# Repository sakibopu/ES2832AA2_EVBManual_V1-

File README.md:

# ES2832AA2_EVBManual_V1 
 ES2832AA2_EVBManual_V1

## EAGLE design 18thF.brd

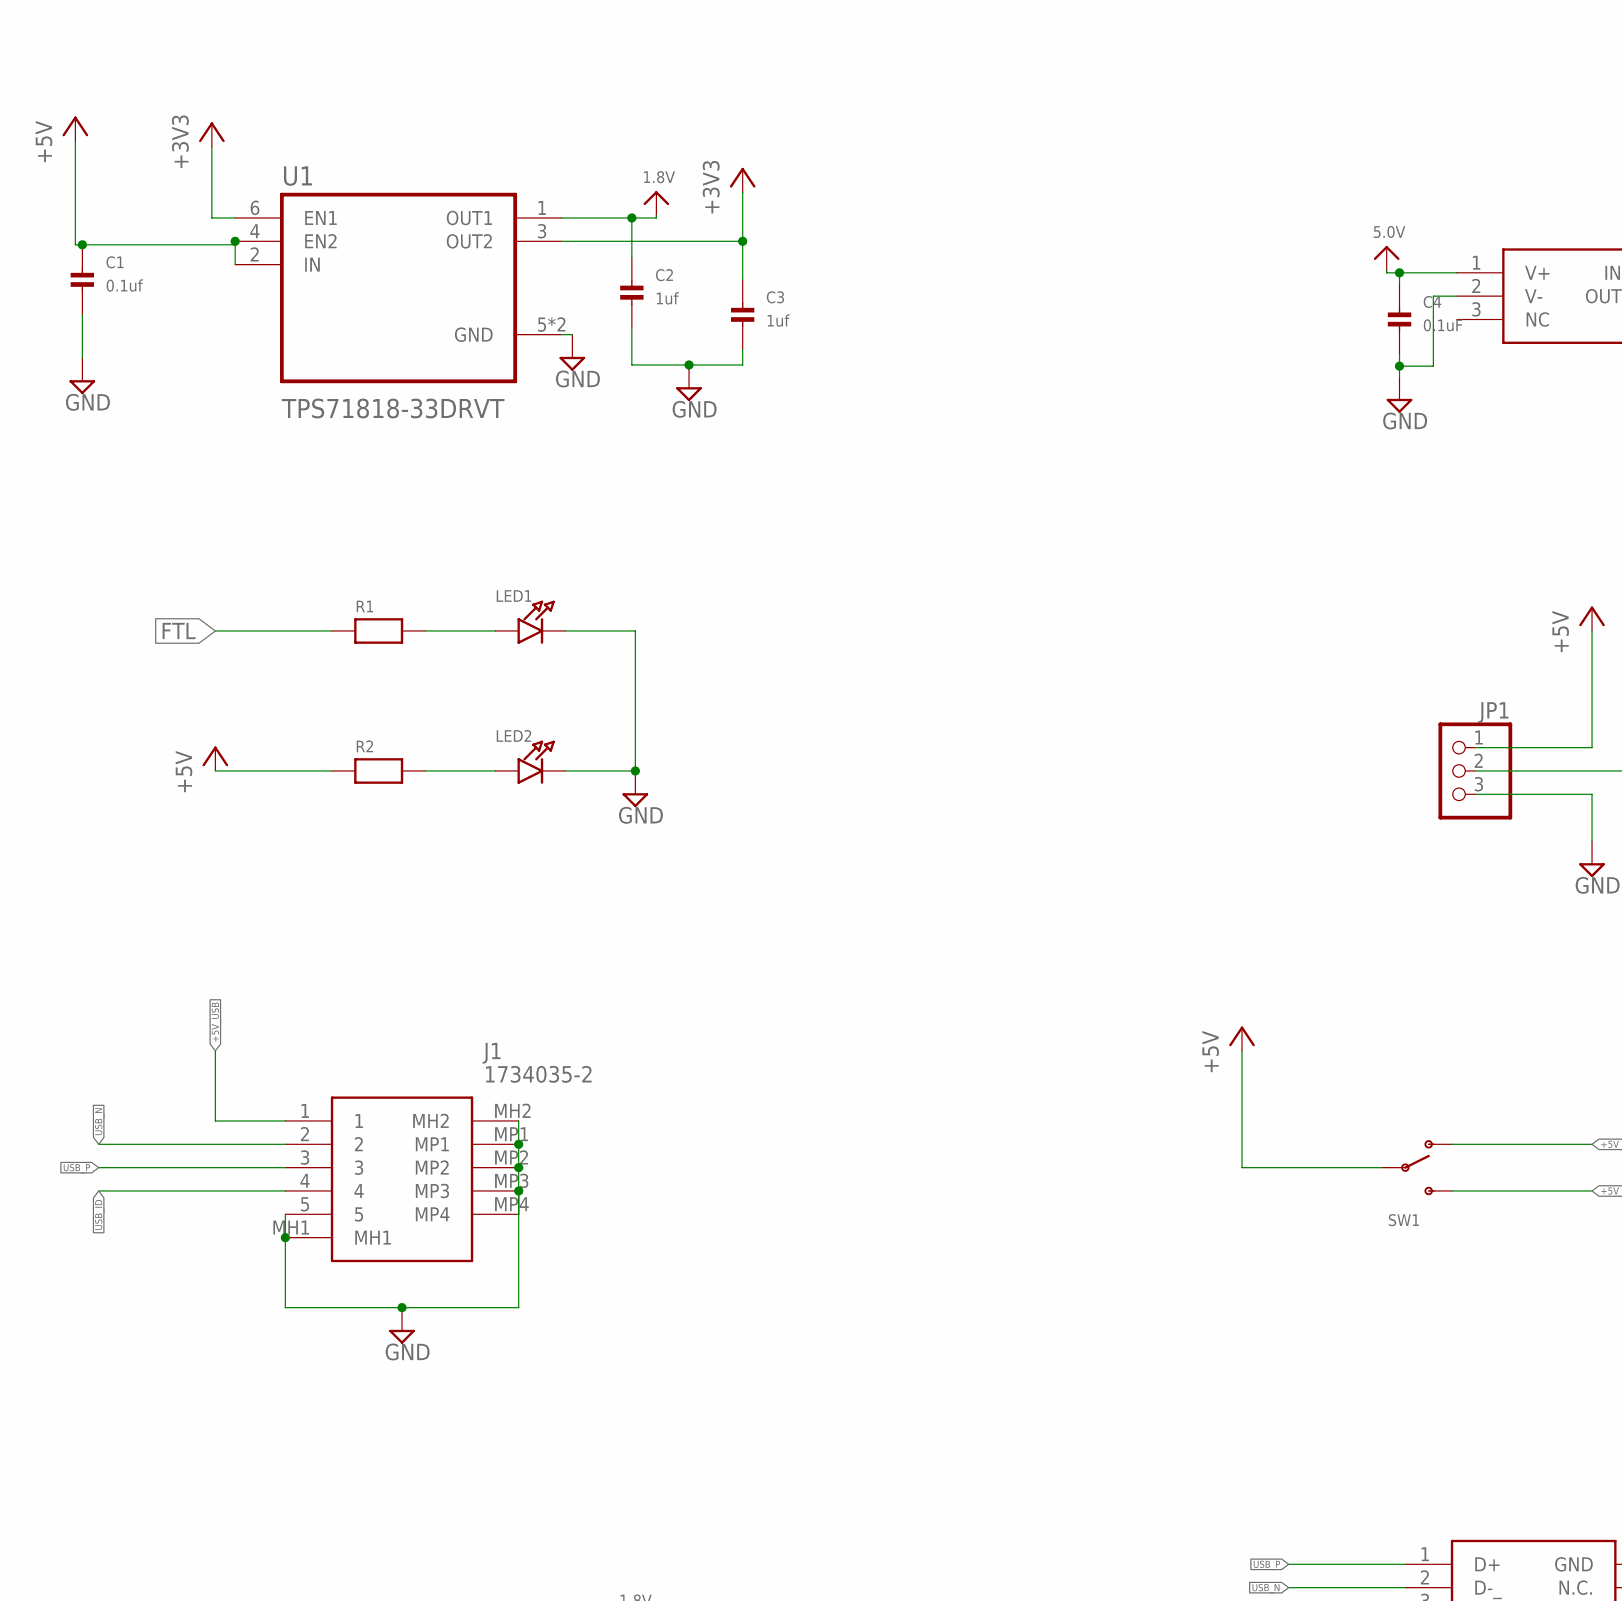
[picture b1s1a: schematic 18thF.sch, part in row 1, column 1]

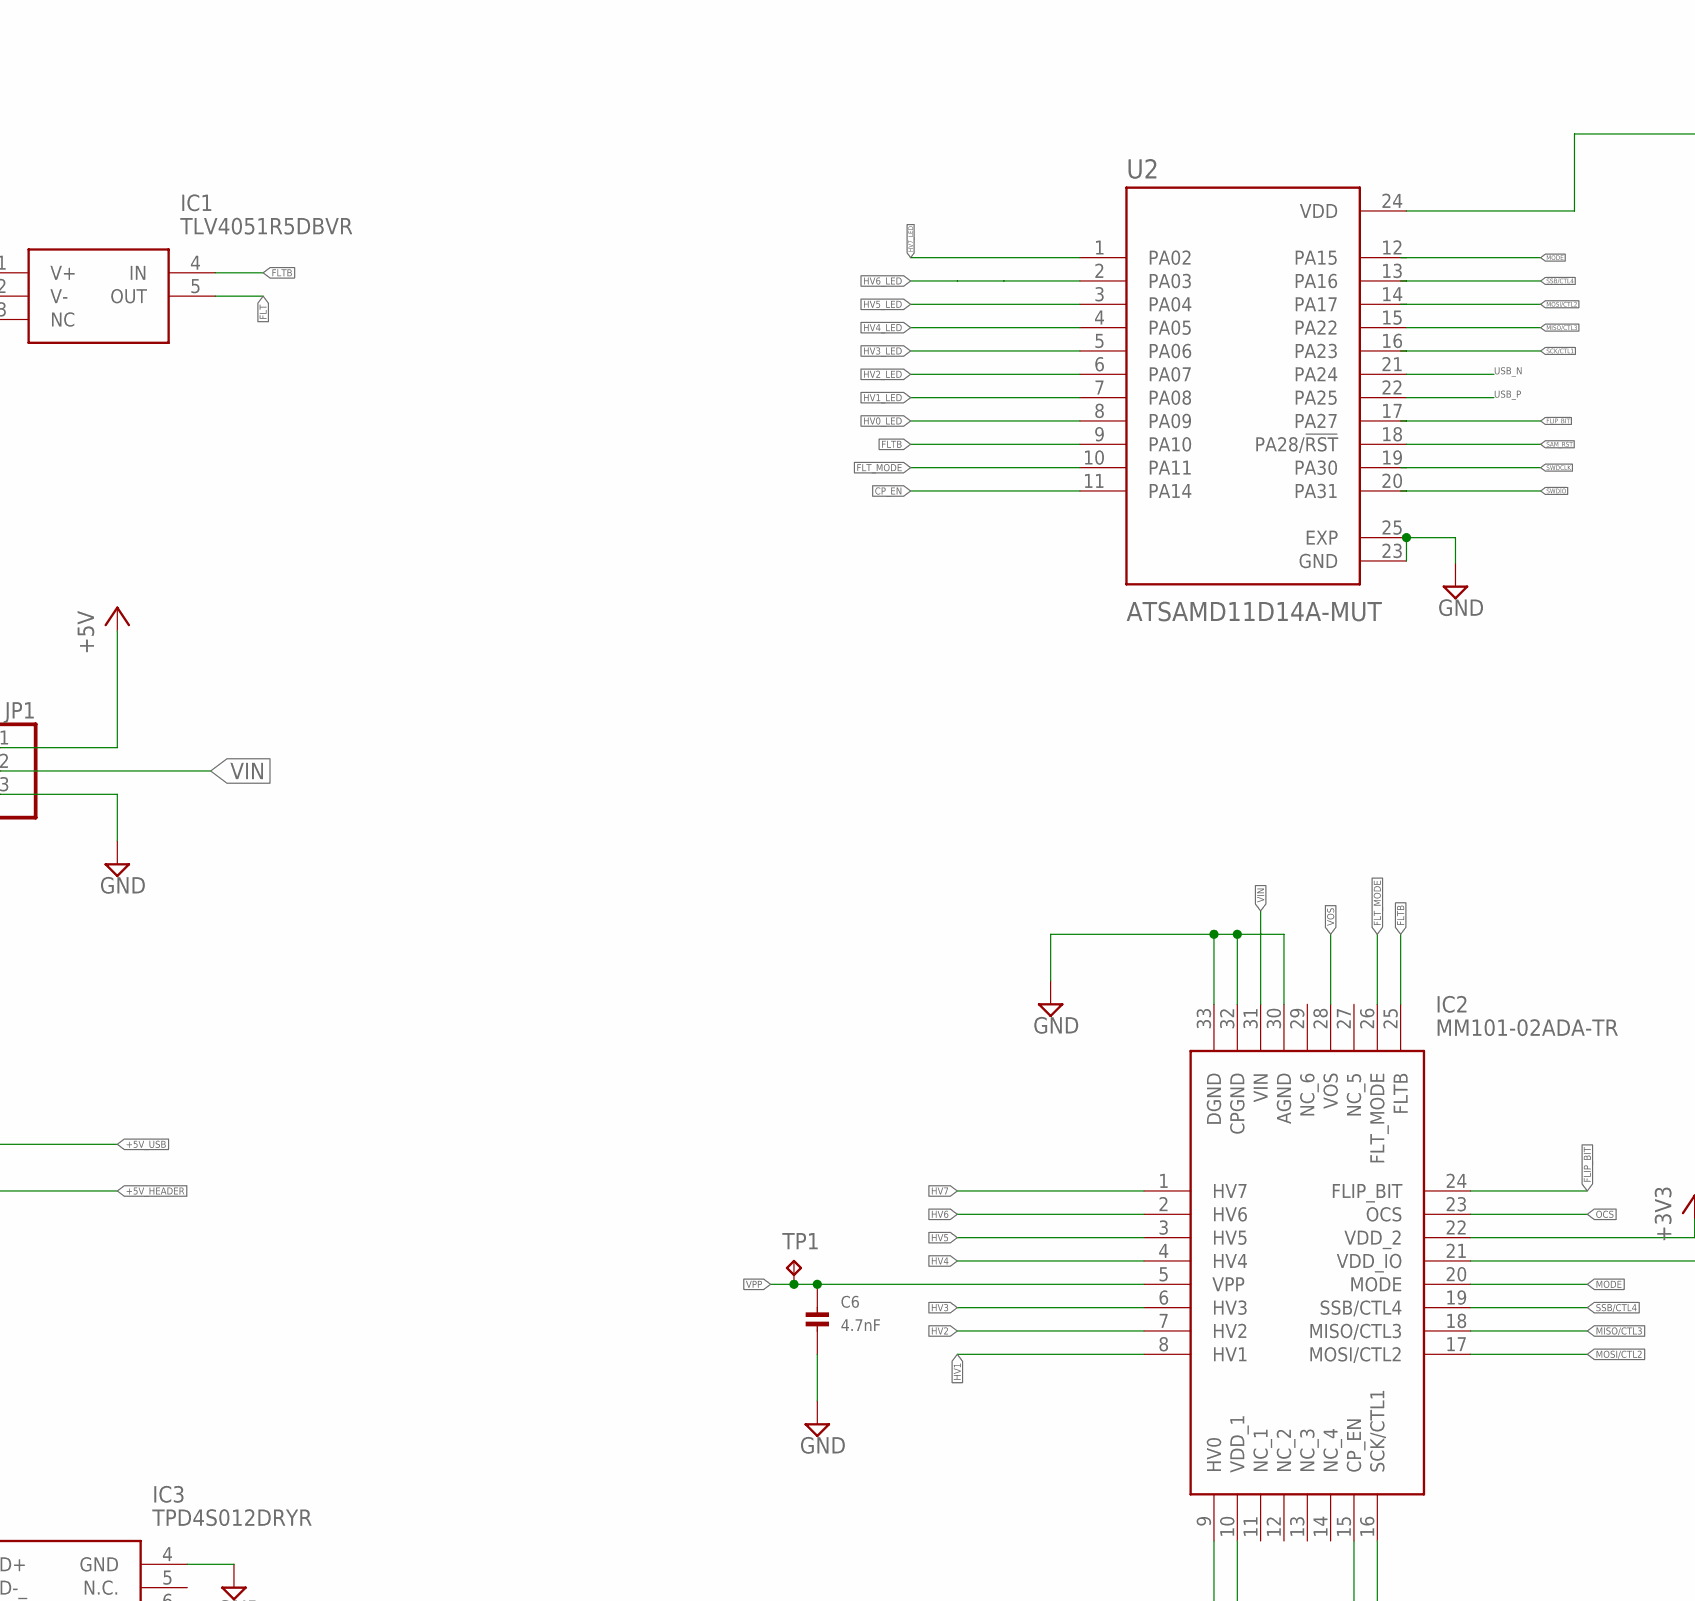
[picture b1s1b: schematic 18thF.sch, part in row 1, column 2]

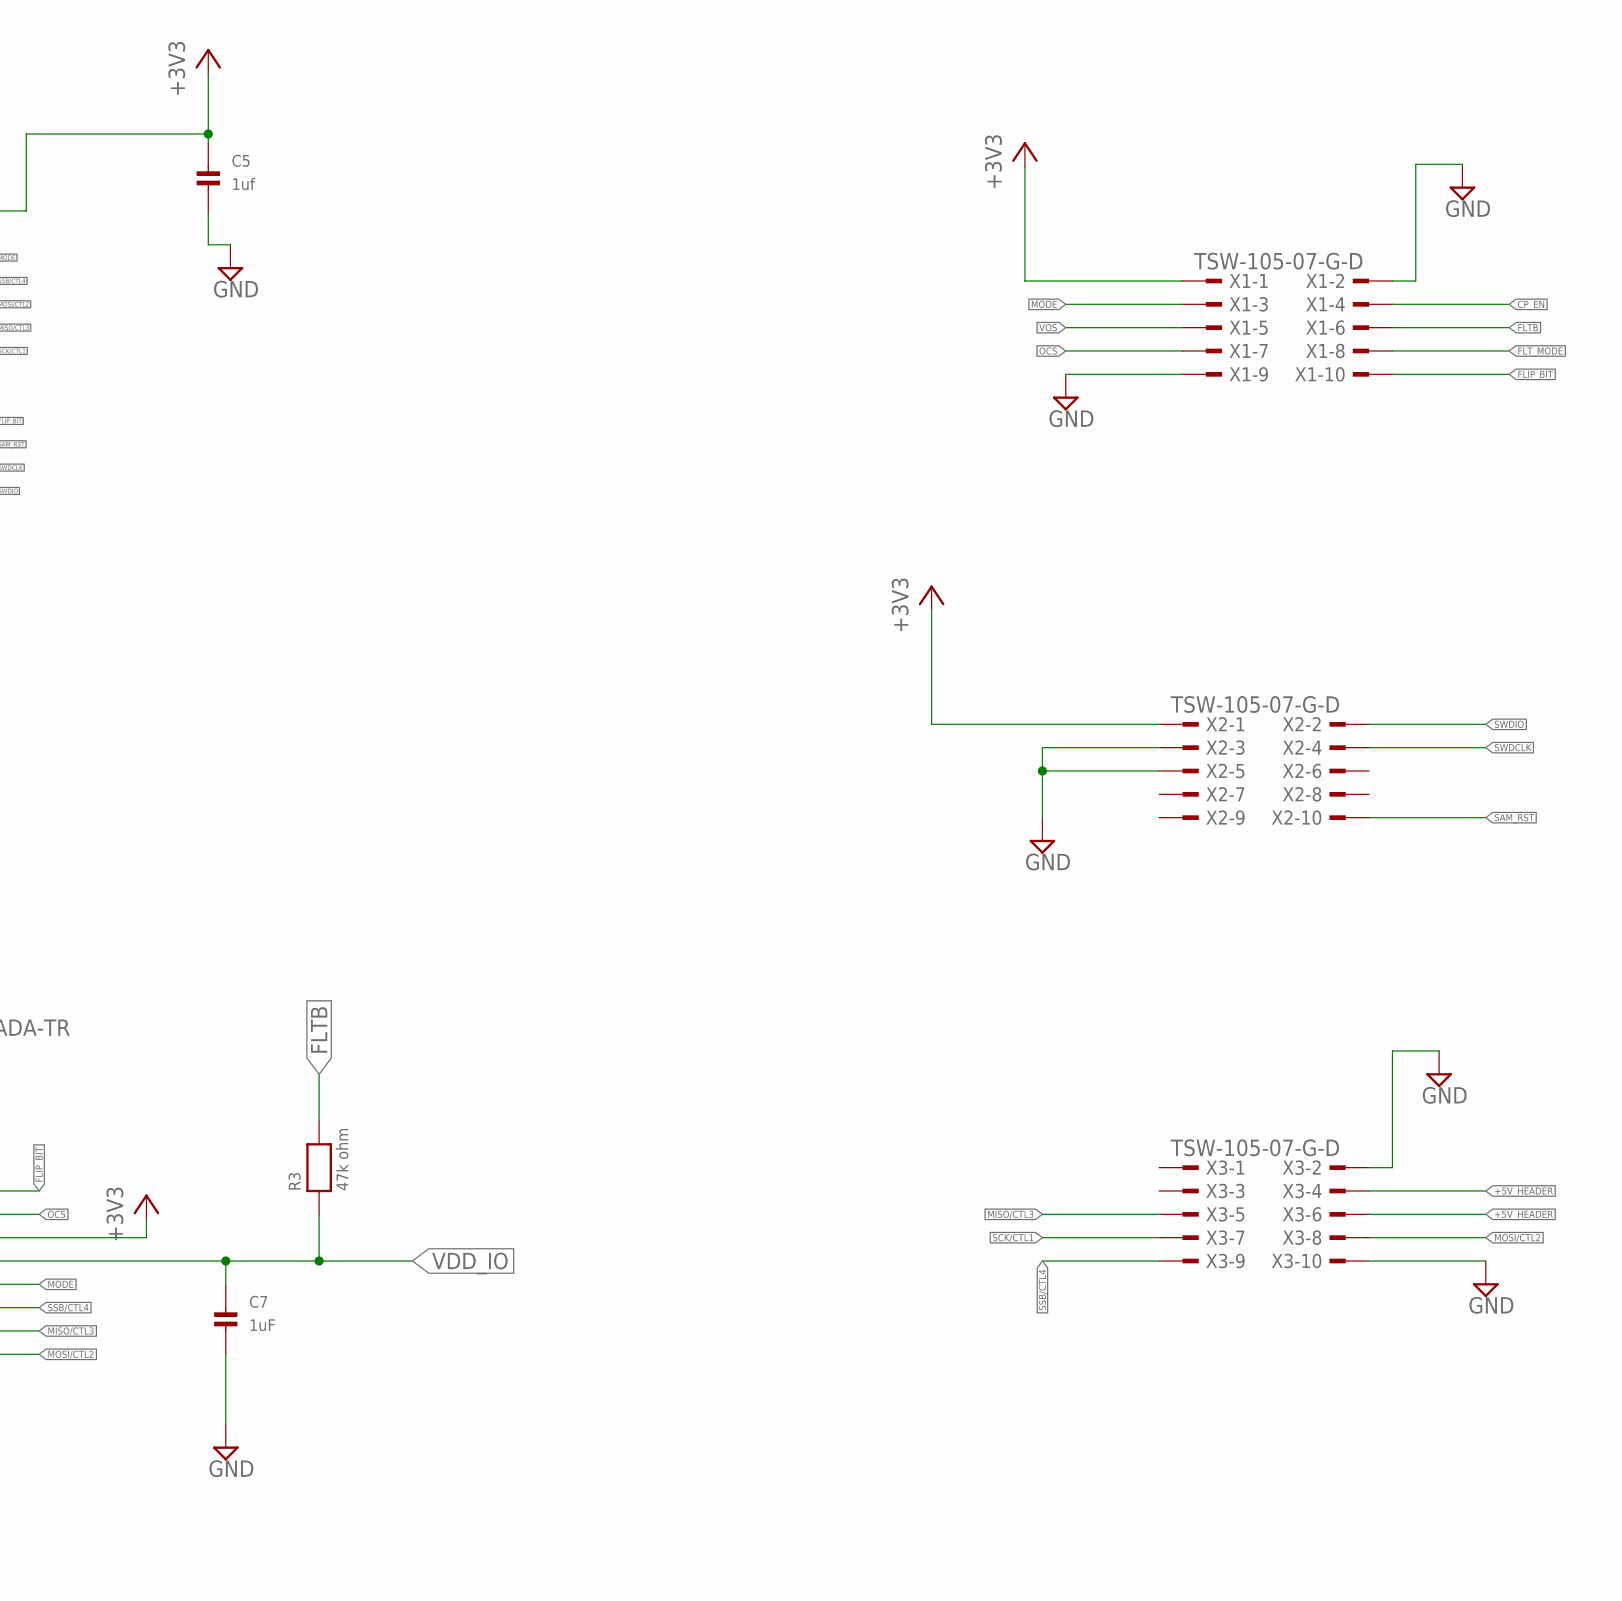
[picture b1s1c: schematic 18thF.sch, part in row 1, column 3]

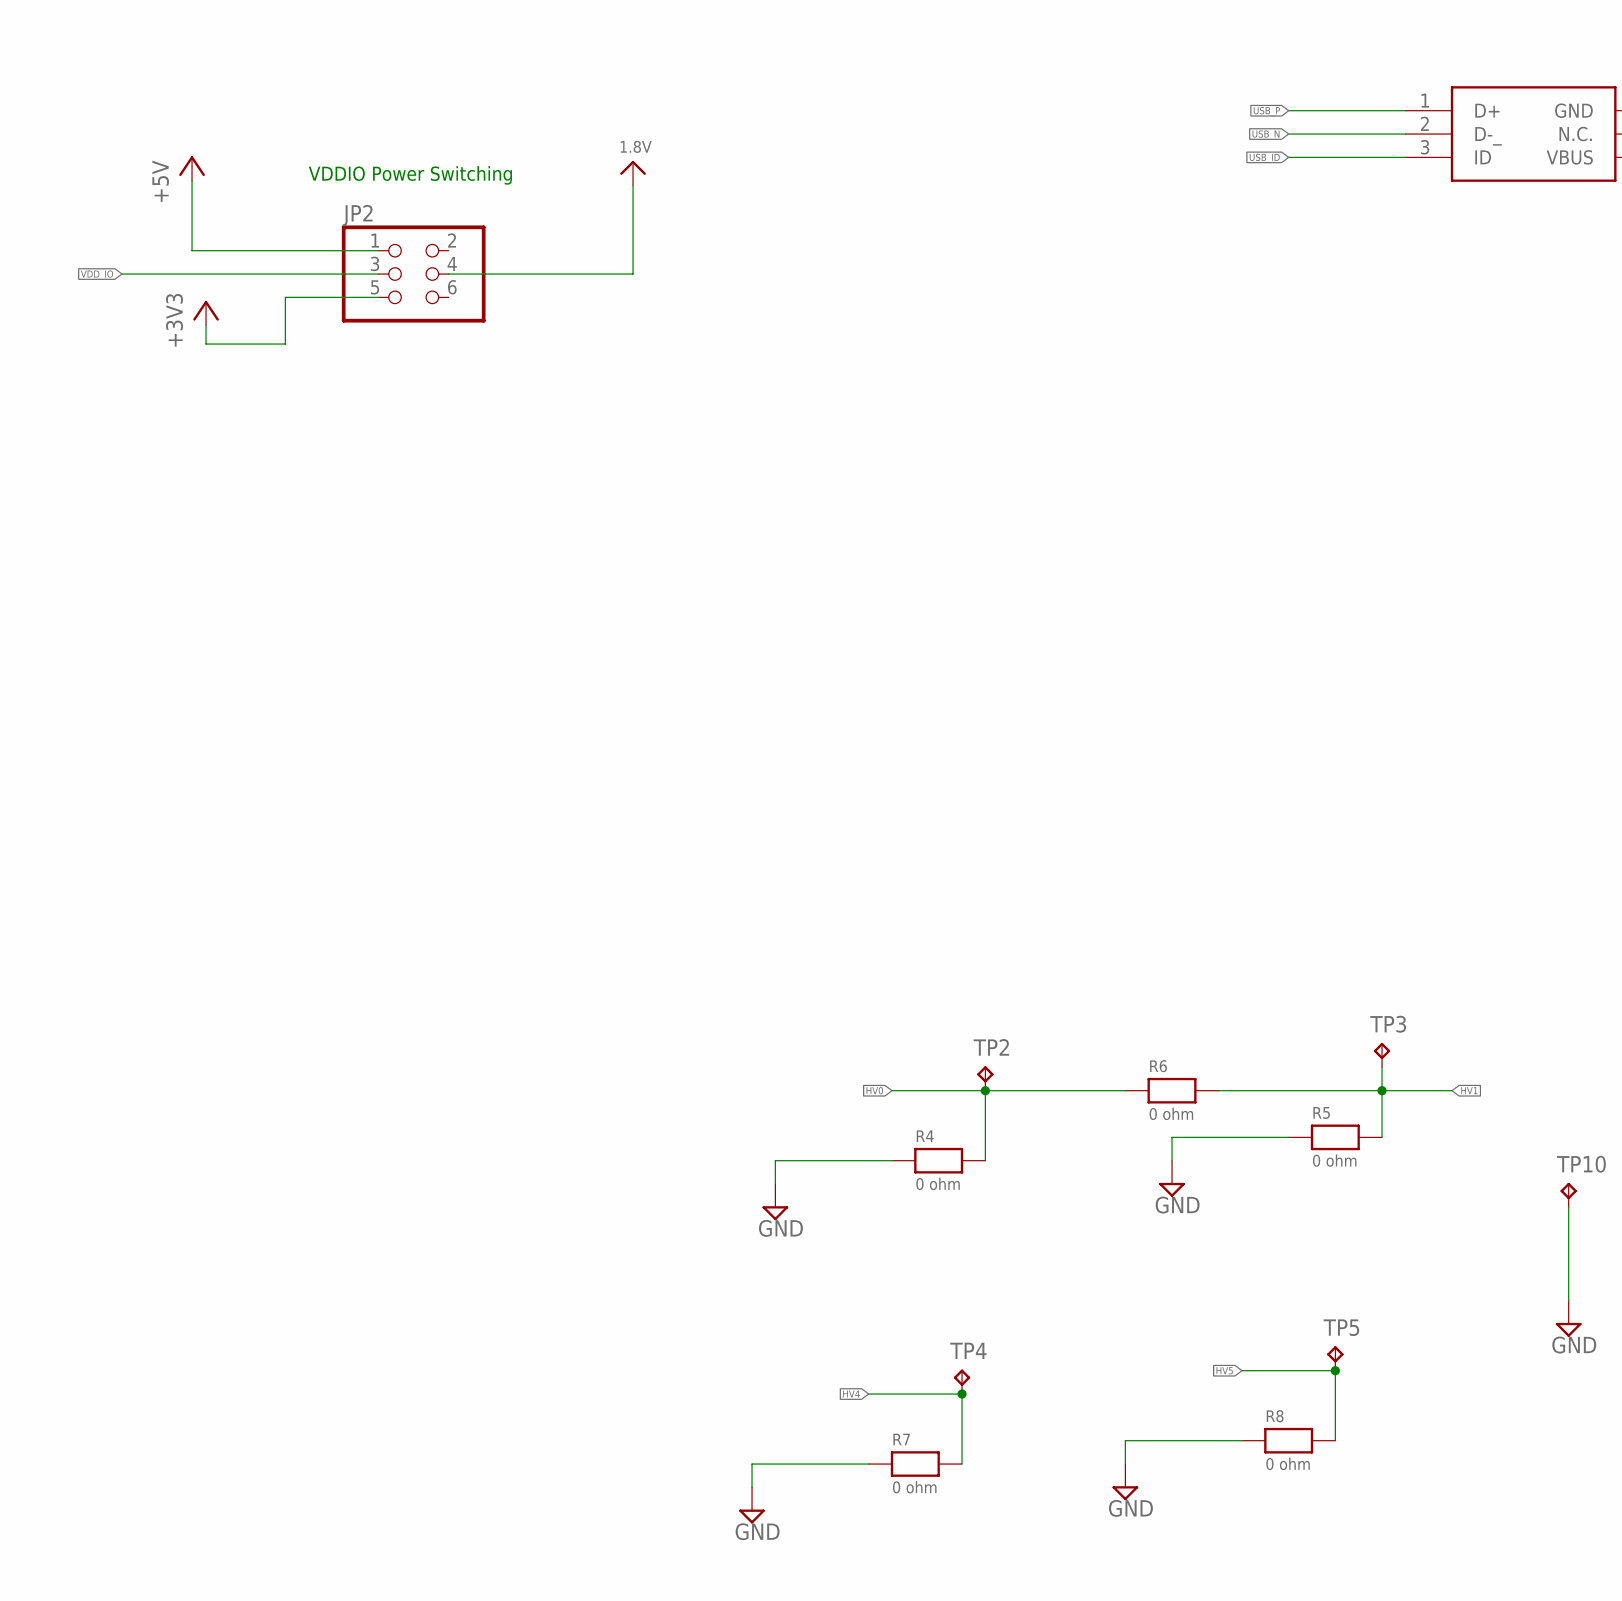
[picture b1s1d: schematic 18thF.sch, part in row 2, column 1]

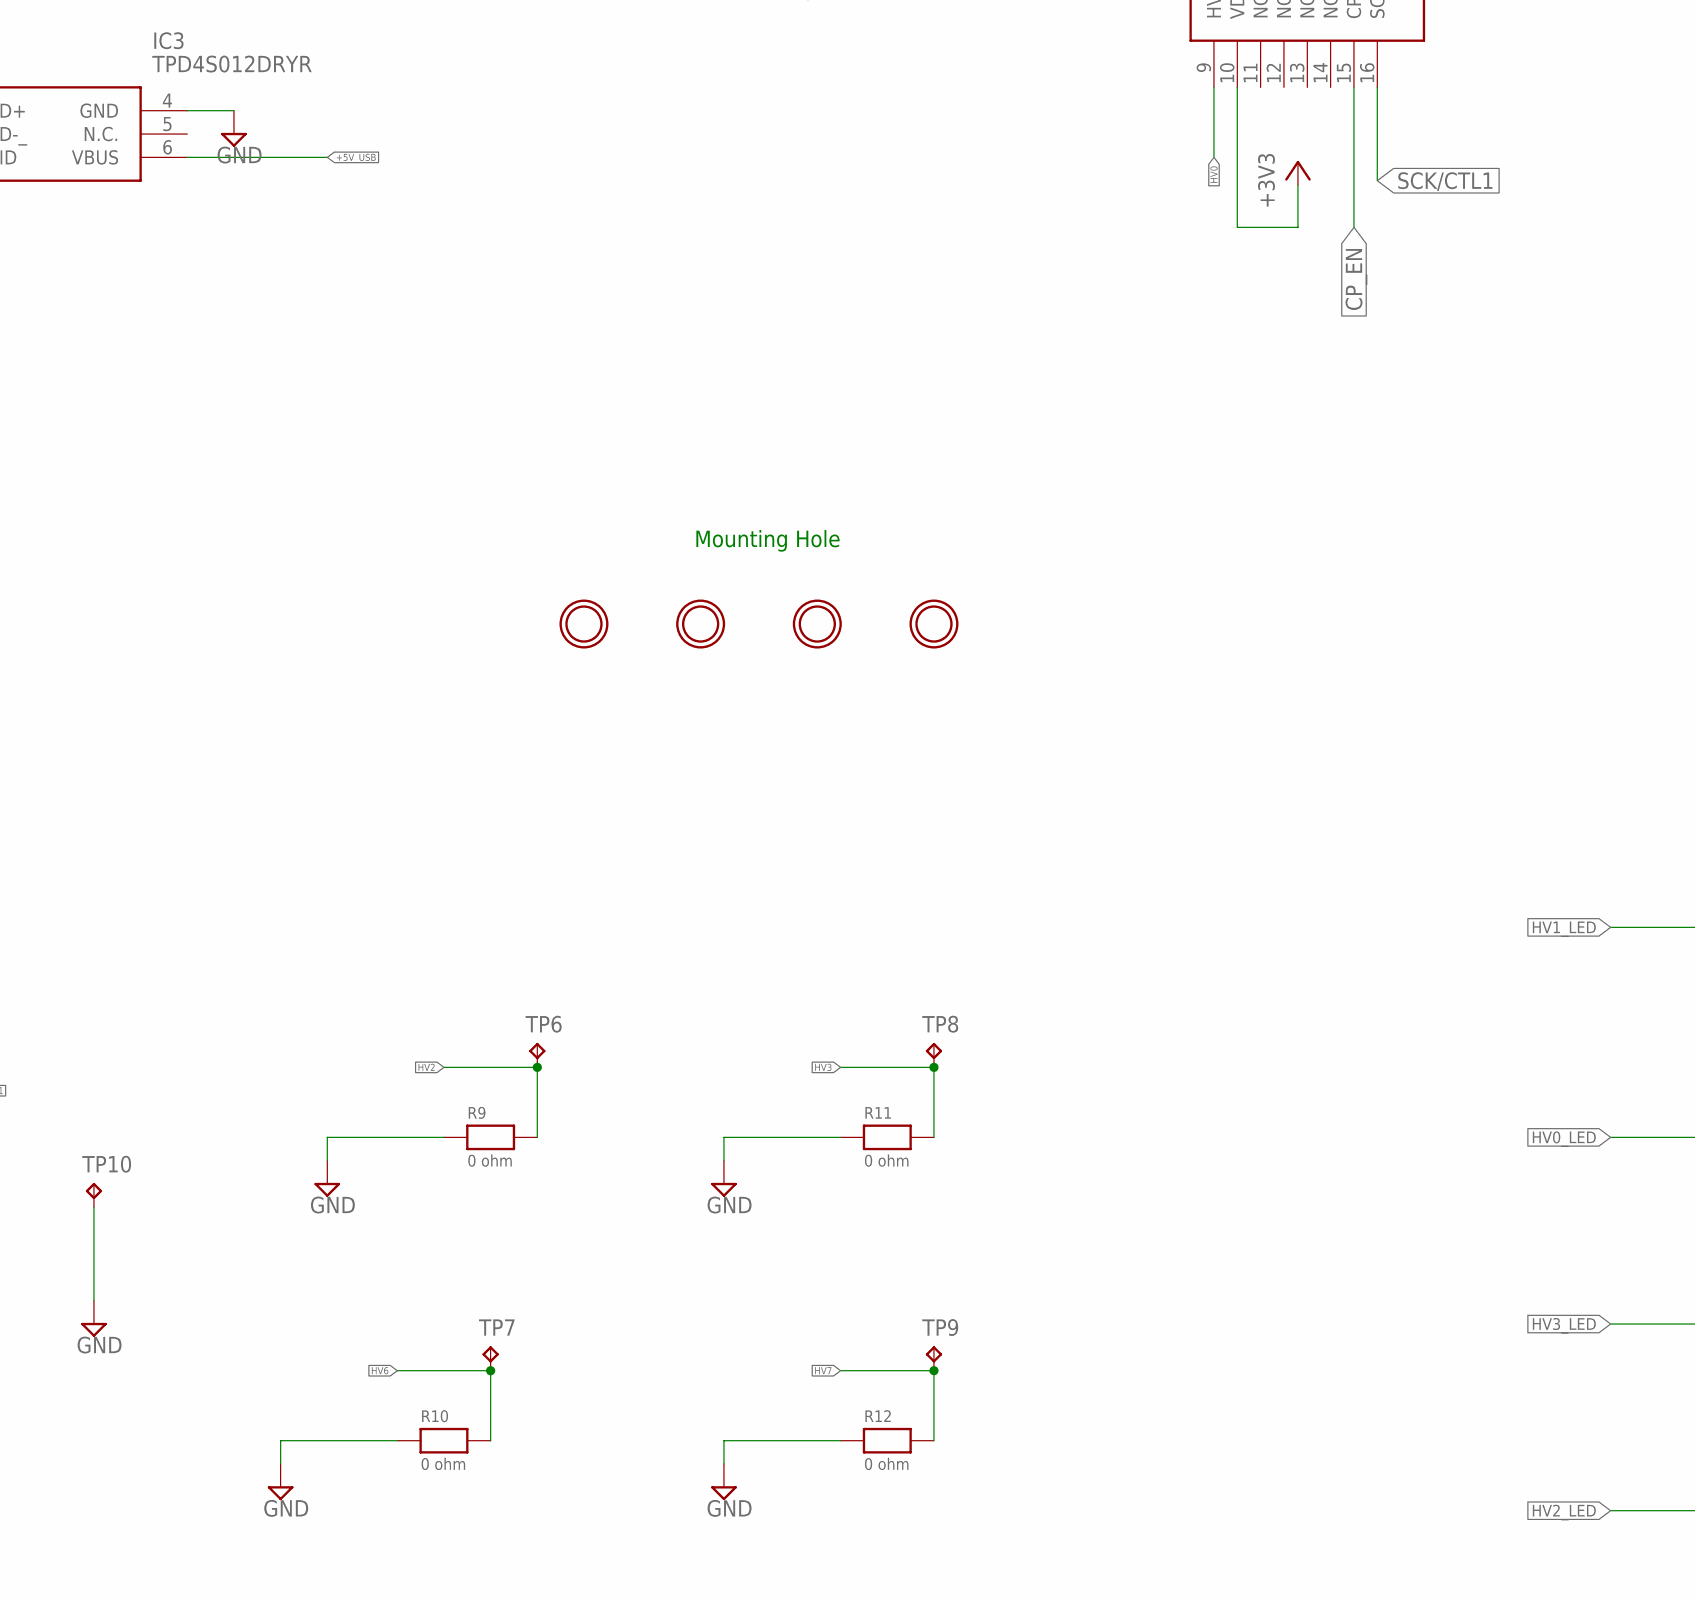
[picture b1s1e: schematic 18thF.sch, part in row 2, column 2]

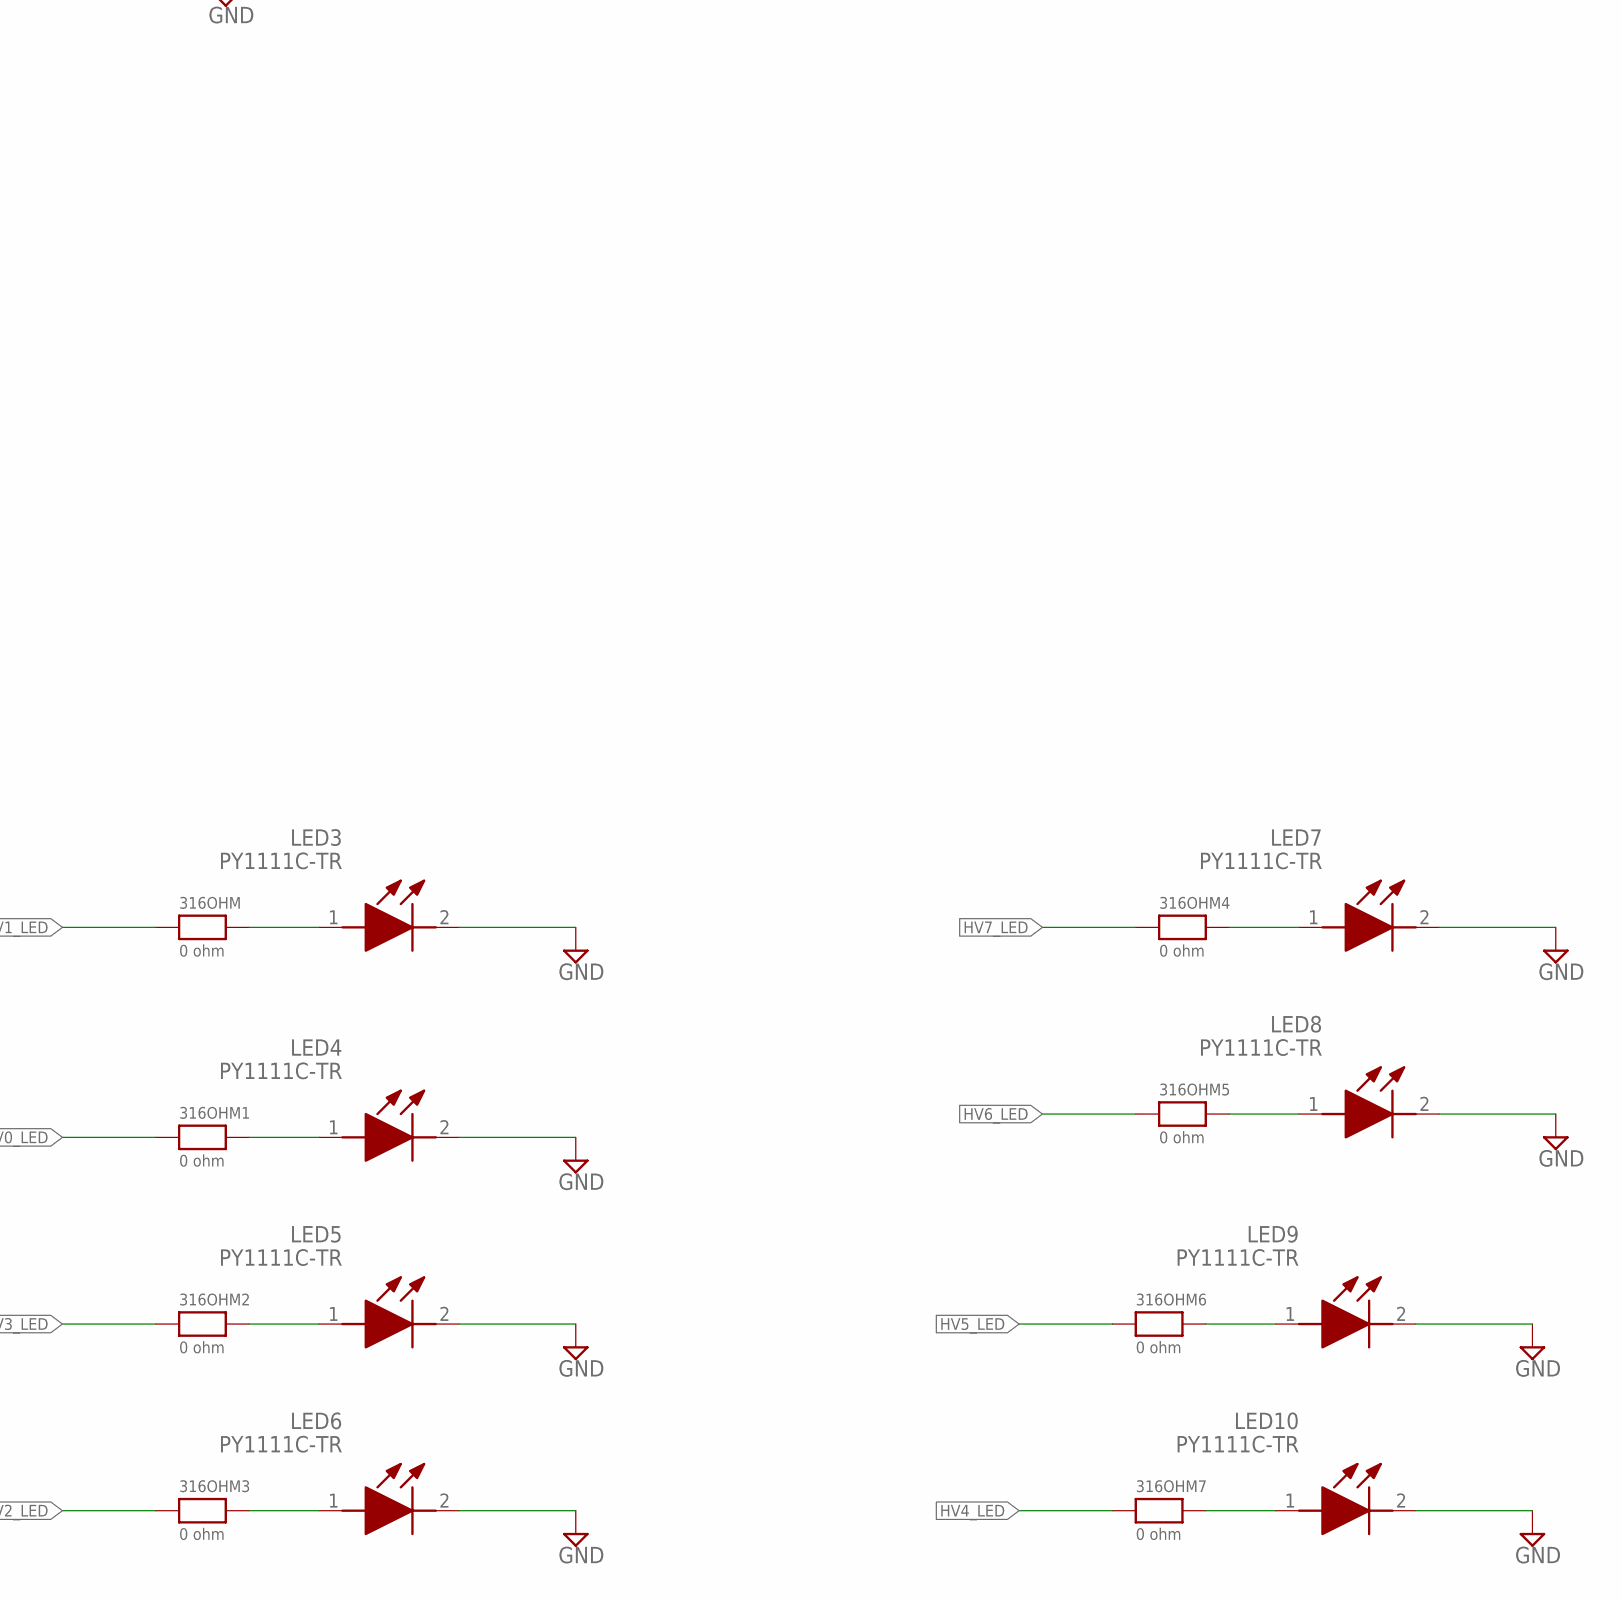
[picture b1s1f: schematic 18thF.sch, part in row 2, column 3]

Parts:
316OHM, 316OHM1, 316OHM2, 316OHM3, 316OHM4, 316OHM5, 316OHM6, 316OHM7: 0 ohm; 0603
C1: 0.1uf; 0603
C2, C3, C5: 1uf; 0603
C4: 0.1uF; 0603
C6: 4.7nF; 0603
C7: 1uF; 0603
IC1: TLV4051R5DBVR; SOT95P280X145-5N
IC2: MM101-02ADA-TR; QFN50P500X500X100-33N
IC3: TPD4S012DRYR
J1: 1734035-2; 17340352
JP1: HEADER-1X3ROUND; 1X03_ROUND
JP2: PINHD-2X3; 2X03
LED1, LED2: LED0603_NOOUTLINE; CHIPLED_0603_NOOUTLINE
LED3, LED4, LED5, LED6, LED7, LED8, LED9, LED10: PY1111C-TR; PY1111CTR
R1, R2: RESISTOR0603; 0603
R3: 47k ohm; 0603
R4, R5, R6, R7, R8, R9, R10, R11, R12: 0 ohm; 0603
SW1: SWITCH_SPDT; SPDT_SMT_SSSS811101
TP1, TP2, TP3, TP4, TP5, TP6, TP7, TP8, TP9, TP10: TPB1,27; B1,27
U1: TPS71818-33DRVT; SON65P200X200X80-7N
U2: ATSAMD11D14A-MUT; QFN50P400X400X90-25N
U$4, U$5, U$6, U$7: MOUNTINGHOLE2.5; MOUNTINGHOLE_2.5_PLATED
X1, X2, X3: TSW-105-07-G-D; TSW-105-XX-G-D

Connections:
1.8V: C2.1, JP2.4, U1.1 (OUT1)
5.0V: C4.1, IC1.1 (V+)
+3V3: C3.1, C5.1, IC2.10 (VDD_1), IC2.22 (VDD_2), JP2.5, U1.3 (OUT2), U1.6 (EN1), U2.24 (VDD), X1.1, X2.1
+5V: C1.1, JP1.1, JP2.1, R2.1, SW1.B, U1.2 (IN), U1.4 (EN2)
+5V_HEADER: SW1.C (S), X3.4, X3.6
+5V_USB: IC3.6 (VBUS), J1.1, SW1.A (O)
CP_EN: IC2.15 (CP_EN), U2.11 (PA14), X1.4
FLIP_BIT: IC2.24 (FLIP_BIT), X1.10
FLTB: IC1.4 (IN), IC2.25 (FLTB), R3.2, U2.9 (PA10), X1.6
FLT_MODE: IC2.26 (FLT_MODE), U2.10 (PA11), X1.8
GND: C1.2, C2.2, C3.2, C4.2, C5.2, C6.2, C7.2, IC1.2 (V-), IC2.30 (AGND), IC2.32 (CPGND), IC2.33 (DGND), IC3.4 (GND), J1.5, J1.MH1, J1.MH2, J1.MP1, J1.MP2, J1.MP3, J1.MP4, JP1.3, LED1.C, LED2.C, LED3.2 (K), LED4.2 (K), LED5.2 (K), LED6.2 (K), LED7.2 (K), LED8.2 (K), LED9.2 (K), LED10.2 (K), R4.1, R5.1, R7.1, R8.1, R9.1, R10.1, R11.1, R12.1, TP10.TP, U1.5 (GND), U1.7 (GND), U2.23 (GND), U2.25 (EXP), X1.2, X1.9, X2.3, X2.5, X3.2, X3.10
HV0: IC2.9 (HV0), R4.2, R6.1, TP2.TP
HV0_LED: 316OHM1.1, U2.8 (PA09)
HV1: IC2.8 (HV1), R5.2, R6.2, TP3.TP
HV1_LED: 316OHM.1, U2.7 (PA08)
HV2: IC2.7 (HV2), R9.2, TP6.TP
HV2_LED: 316OHM3.1, U2.6 (PA07)
HV3: IC2.6 (HV3), R11.2, TP8.TP
HV3_LED: 316OHM2.1, U2.5 (PA06)
HV4: IC2.4 (HV4), R7.2, TP4.TP
HV4_LED: 316OHM7.1, U2.4 (PA05)
HV5: IC2.3 (HV5), R8.2, TP5.TP
HV5_LED: 316OHM6.1, U2.3 (PA04)
HV6: IC2.2 (HV6), R10.2, TP7.TP
HV6_LED: 316OHM5.1, U2.2 (PA03)
HV7: IC2.1 (HV7), R12.2, TP9.TP
HV7_LED: 316OHM4.1, U2.1 (PA02)
MISO/CTL3: IC2.18 (MISO/CTL3), U2.15 (PA22), X3.5
MODE: IC2.20 (MODE), U2.12 (PA15), X1.3
MOSI/CTL2: IC2.17 (MOSI/CTL2), U2.14 (PA17), X3.8
unnamed: LED1.A, R1.2
unnamed: LED2.A, R2.2
unnamed: 316OHM.2, LED3.1 (A)
unnamed: 316OHM1.2, LED4.1 (A)
unnamed: 316OHM2.2, LED5.1 (A)
unnamed: 316OHM3.2, LED6.1 (A)
unnamed: 316OHM4.2, LED7.1 (A)
unnamed: 316OHM5.2, LED8.1 (A)
unnamed: 316OHM6.2, LED9.1 (A)
unnamed: 316OHM7.2, LED10.1 (A)
OCS: IC2.23 (OCS), X1.7
SAM_RST: U2.18 (PA28/!RST), X2.10
SCK/CTL1: IC2.16 (SCK/CTL1), X3.7
SSB/CTL4: IC2.19 (SSB/CTL4), U2.13 (PA16), X3.9
SWDCLK: X2.4
SWDIO: X2.2
USB_ID: IC3.3 (ID), J1.4
USB_N: IC3.2 (D-_), J1.2, U2.21 (PA24)
USB_P: IC3.1 (D+), J1.3, U2.22 (PA25)
VDD_IO: C7.1, IC2.21 (VDD_IO), JP2.3, R3.1
VIN: IC2.31 (VIN), JP1.2
VOS: IC2.28 (VOS), X1.5
VPP: C6.1, IC2.5 (VPP), TP1.TP

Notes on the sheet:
VDDIO Power Switching
Mounting Hole

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
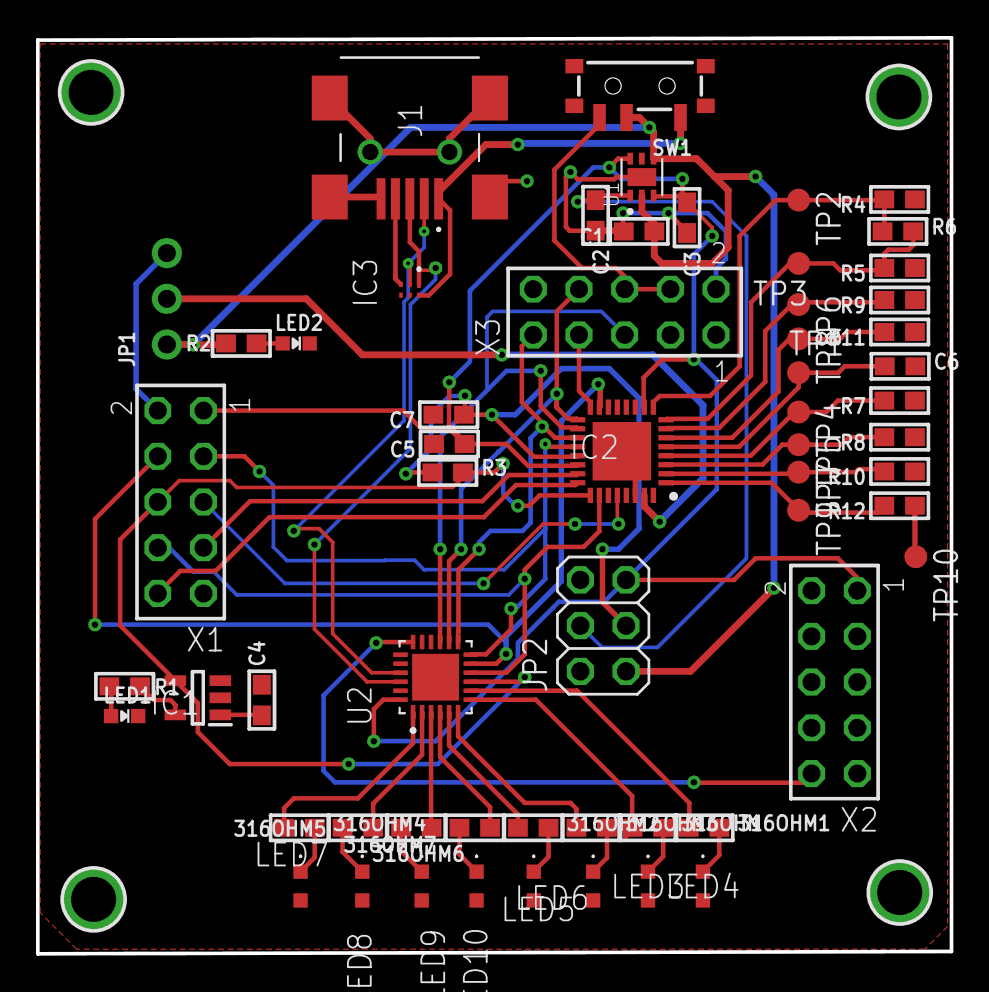
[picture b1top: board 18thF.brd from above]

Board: 2 copper layers, 50.8 x 50.9 mm, 63 parts (0 on the bottom side), 52 nets.

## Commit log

2024-08-16 Add files via upload
    uploaded
2024-08-16 uploaded

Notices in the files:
parts and their libraries:
microbuilder: This work is placed in the public domain, and may be freely used for commercial and non-commercial work with the following conditions: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
